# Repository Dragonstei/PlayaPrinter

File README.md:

# Playa Printer
You can find our project on: https://playaprinter.stadslabrotterdam.nl/

## The Idea

5 years ago Arnold Roosch, then a lab manager at Stadslab Rotterdam, came up with the idea to build a huge 3D dust printer to print objects out of sand at Burning Man Festival. Unfortunately, he wasn’t able to finish his project due to illness. Stadslab Rotterdam decided to continue the building of the printer with the help from friends and family of Arnold, lab employees and students from Rotterdam University of Applied Sciences.

## The Playa Printer

We aim to build a 3D sand printer to create sculptures that can be fully degraded and upcycled after a few days. The “Leave-no-trace” principle of Burning Man Festival is our inspiration. At the International FabLab Conference (FAB15) in Egypt we will be printing with desert sand. Because of the heat and wind the sculptures will dissolve in a few days. 

It is an ongoing project that will be improved and used with different materials by different groups of students.

### Resources:
* https://reprap.org/wiki/RAMPS_1.4
* http://www.geeetech.com/wiki/index.php/Ramps1.4

### Technical information:

Printer unique ID:
6b82af56-c7b9-41e2-99fa-451697f835ac

Stepper motor pin layout (A4988):\
2B = Black\
2A = Green\
1A = Red\
1B = Blue

**Make sure to redefine the steppermotor in configuration.h!**\

**Currently obsolete, printer does not have a screen connected**\
Make sure to download the latest NewLiquidCrystal library here and include it in Arduino:\
https://bitbucket.org/fmalpartida/new-liquidcrystal/downloads/

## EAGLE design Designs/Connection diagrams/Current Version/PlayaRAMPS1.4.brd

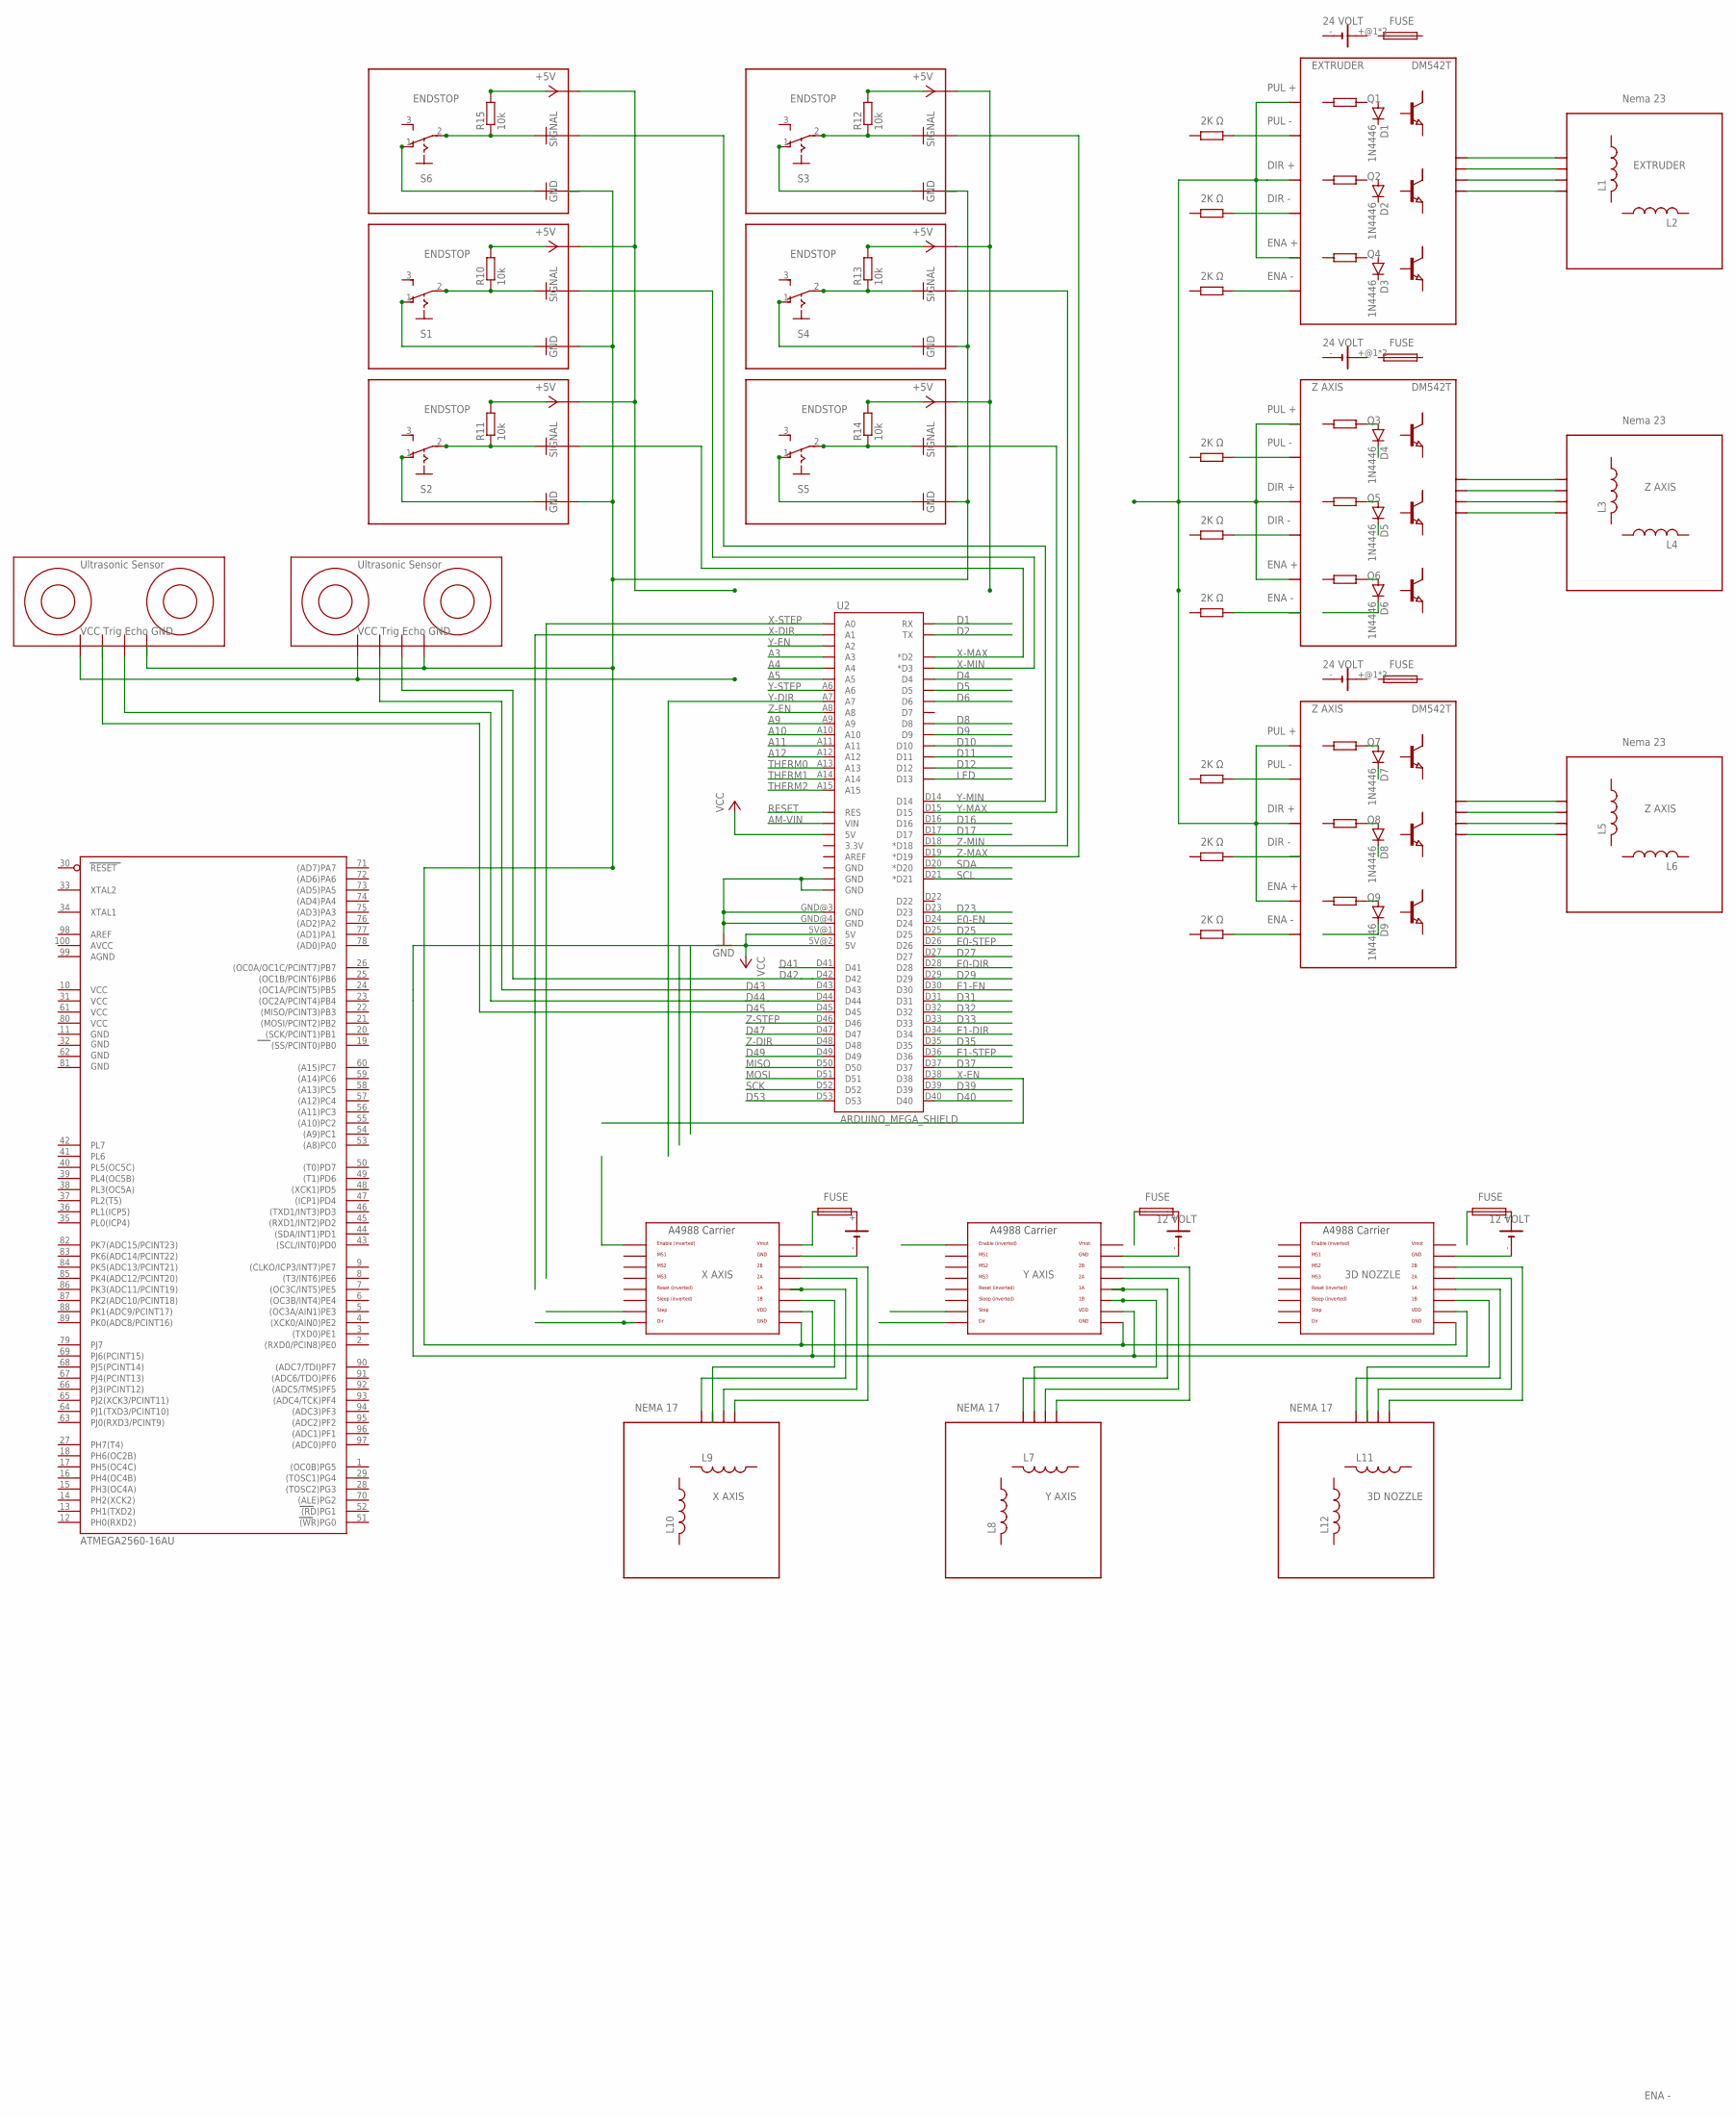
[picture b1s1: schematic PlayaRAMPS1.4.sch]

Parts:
D1, D2, D3, D4, D5, D6, D7, D8, D9: 1N4446; DO35-10
F1, F2, F3, F4, F5, F6: QPL
G1, G5, G6: 10MM_SM_COIN_CELL_CLIP
G2, G3, G4: CH291-1220LF
IC3: ATMEGA2560-16AU; TQFP100
L1, L2, L3, L4, L5, L6, L7, L8, L9, L10, L11, L12: L-US0204/5; 0204/5
Q1, Q2, Q3, Q4, Q5, Q6, Q7, Q8, Q9: NPN-TRANSISTIOR-2COLSOT143; SOT143
R10, R11, R12, R13, R14, R15: 10k; 0204/7
R16, R17, R18, R19, R20, R21, R22, R23, R24: R; R0805
S1, S2, S3, S4, S5, S6: 255SB
U2: ARDUINO_MEGA_SHIELD
X1, X2, X3: A4988BREAKOUT

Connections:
+5V: R10.2, R11.2, R12.2, R13.2, R14.2, R15.2
A3: U2.A3
A4: U2.A4
A5: U2.A5
A9: U2.A9
A10: U2.A10
A11: U2.A11
A12: U2.A12
AGND: IC3.99 (AGND)
AM-VIN: U2.VIN
AVCC: IC3.100 (AVCC)
D1: U2.RX
D2: U2.TX
D4: U2.D4
D5: U2.D5
D6: U2.D6
D8: U2.D8
D9: U2.D9
D10: U2.D10
D11: U2.D11
D12: U2.D12
D16: U2.D16
D17: U2.D17
D23: U2.D23
D25: U2.D25
D27: U2.D27
D29: U2.D29
D31: U2.D31
D32: U2.D32
D33: U2.D33
D35: U2.D35
D37: U2.D37
D39: U2.D39
D40: U2.D40
D41: U2.D41
D42: U2.D42
D43: U2.D43
D44: U2.D44
D45: U2.D45
D47: U2.D47
D49: U2.D49
D53: U2.D53
E0-DIR: U2.D28
E0-EN: U2.D24
E0-STEP: U2.D26
E1-DIR: U2.D34
E1-EN: U2.D30
E1-STEP: U2.D36
GND: IC3.11 (GND), R10.1, R11.1, R12.1, R13.1, R14.1, R15.1, S1.1 (O), S1.2, S2.1 (O), S2.2, S3.1 (O), S3.2, S4.1 (O), S4.2, S5.1 (O), S5.2, S6.1 (O), S6.2, U2.GND@0 (GND), U2.GND@1 (GND), U2.GND@3 (GND), U2.GND@4 (GND)
GND1: IC3.32 (GND1)
GND2: IC3.62 (GND2)
GND3: IC3.81 (GND3)
LED: U2.D13
MISO: U2.D50
MOSI: U2.D51
unnamed: F1.2, G2.+
unnamed: F2.2, G3.+
unnamed: F3.2, G4.+
unnamed: G4.-, X3.GND
unnamed: G3.-, X2.GND
unnamed: G2.-, X1.GND
unnamed: F1.1, X1.VMOT
unnamed: X1.GND@0 (GND), X2.GND@0 (GND), X3.GND@0 (GND)
RESET: U2.RES
SCK: U2.D52
SCL: U2.D21 (*D21)
SDA: U2.D20 (*D20)
THERM0: U2.A13
THERM1: U2.A14
THERM2: U2.A15
VCC: IC3.10 (VCC), U2.5V@0 (5V), U2.5V@1 (5V), U2.5V@2 (5V), X1.VDD, X2.VDD, X3.VDD
VCC1: IC3.31 (VCC1)
VCC2: IC3.61 (VCC2)
VCC3: IC3.80 (VCC3)
VMOT: X2.VMOT, X3.VMOT
X-DIR: U2.A1
X-DIR1: X1.DIR
X-EN: U2.D38
X-EN1: X1.EN
X-MAX: U2.D2 (*D2)
X-MIN: U2.D3 (*D3)
X-STEP: U2.A0
X-STEP1: X1.STEP
Y-DIR: U2.A7
Y-DIR1: X2.DIR
Y-EN: U2.A2
Y-MAX: U2.D15
Y-MIN: U2.D14
Y-STEP: U2.A6
Z-DIR: U2.D48
Z-EN: U2.A8
Z-MAX: U2.D19 (*D19)
Z-MIN: U2.D18 (*D18)
Z-STEP: U2.D46

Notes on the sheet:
ENA -
NEMA 17
PUL -
PUL +
DIR +
DIR -
ENA +
12 VOLT
X AXIS
Y AXIS
3D NOZZLE
2K Ω
Ultrasonic Sensor
VCC Trig Echo GND
FUSE
Nema 23
DM542T
24 VOLT
Z AXIS
EXTRUDER
ENDSTOP

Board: 2 copper layers, 68 parts (0 on the bottom side), 12 nets, no tracks yet.

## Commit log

2019-07-30 Transfer files from GitLab to GitHub
2019-07-30 Create empty
2019-07-30 Create Parts list
2019-07-30 Update Parts list
2019-07-30 Rename Parts list to Parts list.md
